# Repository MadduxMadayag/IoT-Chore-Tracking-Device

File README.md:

# IoT Chore Tracking Device with Discord Integration

## Overview

Chore Tracker is a smart home device designed to help roommates stay organized by making chore assignments visible, interactive, and easy to manage. Instead of relying on sticky notes or text messages, roommates interact with a physical tabletop display synchronized with a Discord bot. Chores can be assigned digitally while the custom-built hardware provides an always-visible reminder inside the home. The project combines embedded systems, PCB design, CAD, Python development, and Discord API integration into a single product.

For more information, check our **[team's website](https://ejhsu0.wixsite.com/my-site-1)**

## Contributors
**Maddux Madayag, Yu-Han Lou, and Elisabeth Hsu**

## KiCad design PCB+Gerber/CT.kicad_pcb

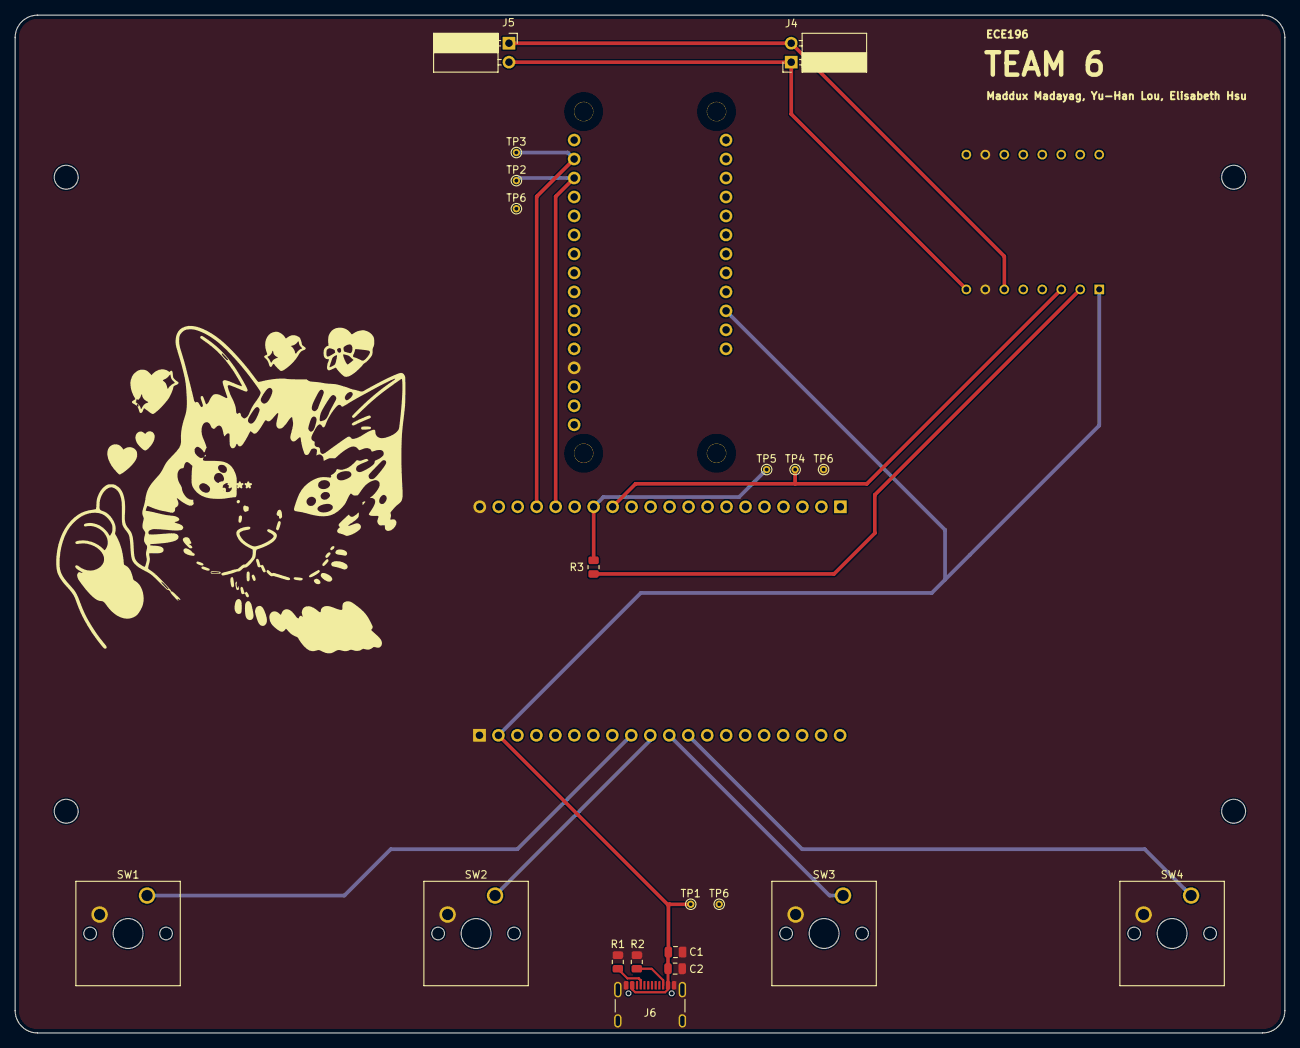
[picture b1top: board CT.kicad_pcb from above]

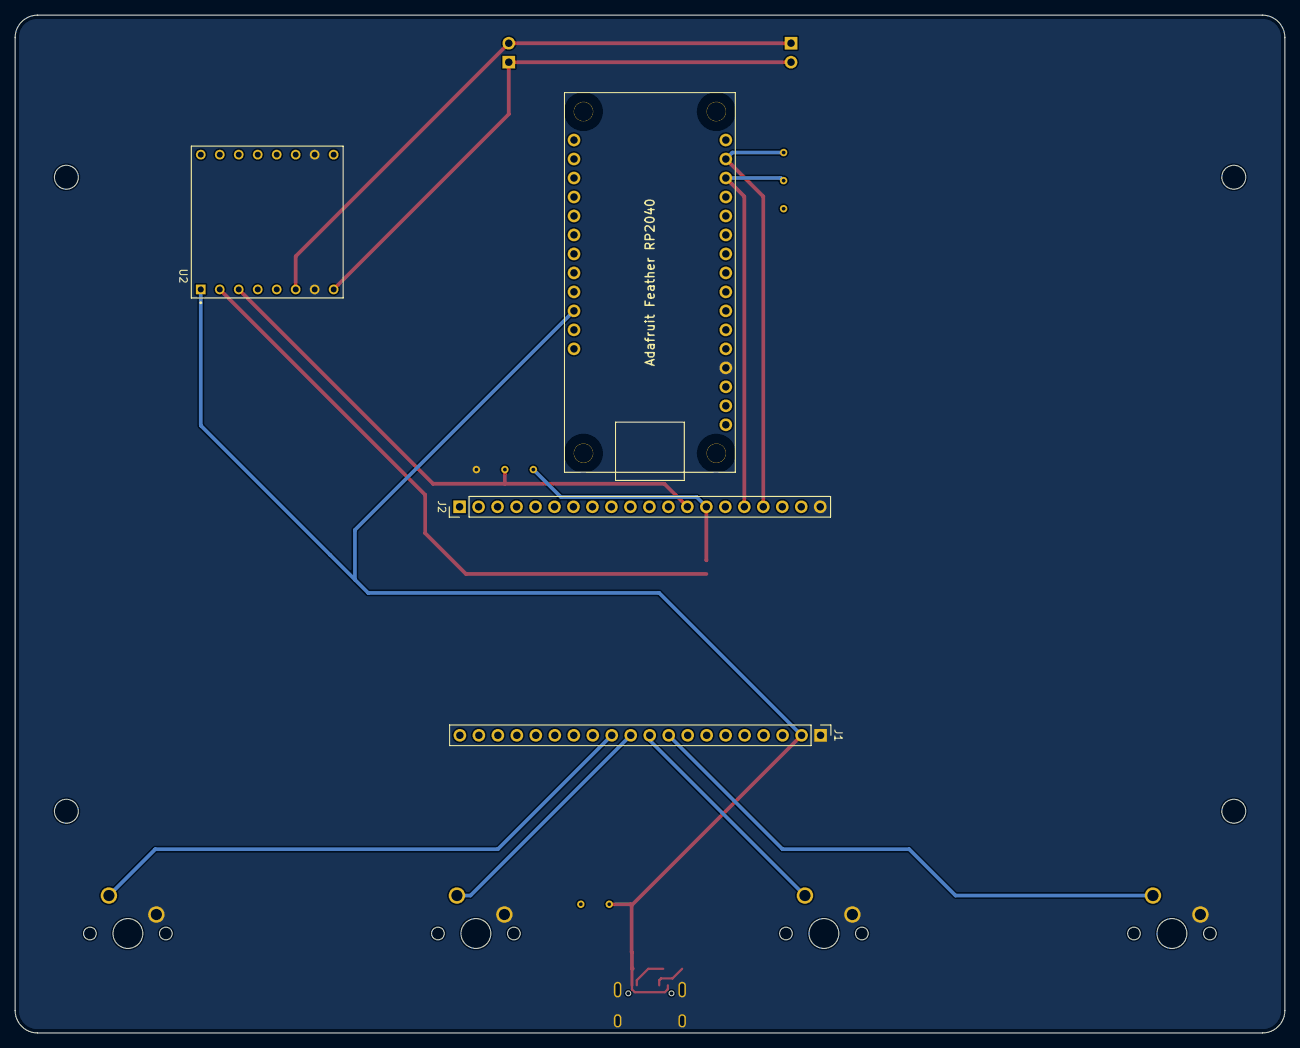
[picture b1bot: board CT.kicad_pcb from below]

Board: 2 copper layers, 169.9 x 136.2 mm, 24 parts (4 on the bottom side), 15 nets.

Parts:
C1: 0.1uF; C_0805_2012Metric
C2: 10uF; C_0805_2012Metric
J1, J2: Conn_01x20_Pin; PinHeader_1x20_P2.54mm_Vertical
J4, J5: Conn_01x02_Socket; PinSocket_1x02_P2.54mm_Horizontal
J6: USB_C_Receptacle_USB2.0_16P; USB_C_Receptacle_GCT_USB4105-xx-A_16P_TopMnt_Horizontal
R1, R2: 5.1k; R_0805_2012Metric
R3: 1k; R_0805_2012Metric
SW1, SW2, SW3, SW4: CherryMX; SW_Cherry_MX_1.00u_PCB
TP1, TP2, TP3, TP4, TP5, TP6, TP6#2, TP6#3: TestPoint; TestPoint_THTPad_D1.0mm_Drill0.5mm
U1: Adafruit-Feather-RP2040
U2: DFR0299; MODULE_DFR0299

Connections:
+5V: C1.1, C2.1, J1.2, J6.A4 (VBUS), J6.A9 (VBUS), J6.B4 (VBUS), J6.B9 (VBUS), TP1.1, U1.26 (Vbus), U2.1 (VCC)
Column 0: J1.9, SW1.1
Column 1: J1.10, SW2.1
Column 2: J1.11, SW3.1
Column 3: J1.12, SW4.1
DF->ESP32: J2.13, TP4.1, U2.3 (TX)
ESP32->DF: J2.14, R3.2, TP5.1
ESP32->RP2040: J2.16, TP2.1, U1.14 (RX/CS/GPIO1)
GND: C1.2, C2.2, J1.1, J2.20, J6.A1 (GND), J6.A12 (GND), J6.B1 (GND), J6.B12 (GND), J6.S1 (SHIELD), R1.2, R2.2, SW1.2, SW2.2, SW3.2, SW4.2, TP6#2.1, U1.4 (GND), U2.7 (GND), U2.10 (GND)
unnamed: J6.A5 (CC1), R1.1
unnamed: J6.B5 (CC2), R2.1
unnamed: R3.1, U2.2 (RX)
RP2040->ESP32: J2.17, TP3.1, U1.15 (TX/GPIO0)
Speaker+: J4.2, J5.1, U2.6 (SPK1)
Speaker-: J4.1, J5.2, U2.8 (SPK2)
